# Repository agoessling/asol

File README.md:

# A Street Of Light (ASOL)
## Solar-powered LED streetlamp for A Liter Of Light (ALOL)
This design attempts to be a low-cost solar battery charger combined with a LED
driver that can be assembled and built by individuals with a large range of
experience.  The design was made using [EagleCad](http://www.cadsoftusa.com/)
and resides in the "hw" directory.  Documentation resides in the "docs"
directory.  This includes a PDF print of the schematic and PCB, a Bill Of
Materials (BOM), a design document, and the manufacturing Gerber files.  This
design is open-source and is licensed under the CERN Open Hardware License
([OHL](http://www.ohwr.org/projects/cernohl/wiki)).  It can be found in the
"license" directory.

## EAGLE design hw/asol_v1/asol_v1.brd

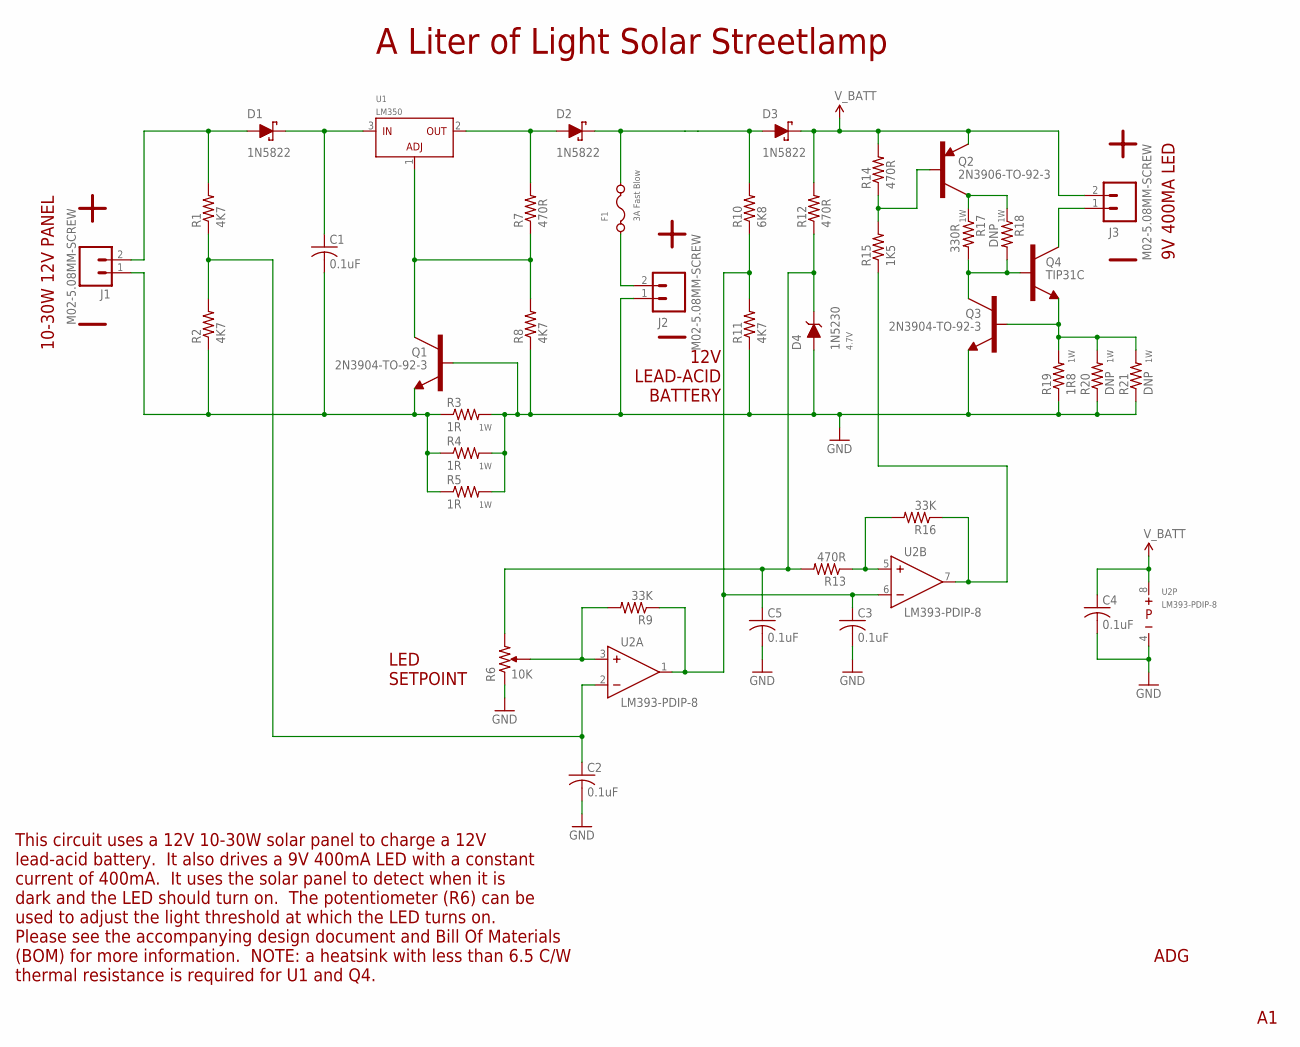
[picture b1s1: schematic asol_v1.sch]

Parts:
C1, C2, C3, C4, C5: 0.1uF; C025-025X050
D1, D2, D3: 1N5822; DO-201AD
D4: 1N5230; DO-35; VOLTAGE 4.7V
F1: 3A Fast Blow; FUSE-5X20MM
J1, J2, J3: M02-5.08MM-SCREW; SCREW-TERMINAL-5.08MM-1X2
Q1, Q3: 2N3904-TO-92-3; TO-92-3
Q2: 2N3906-TO-92-3; TO-92-3
Q4: TIP31C; TO-220-3
R1, R2, R8, R11: 4K7; 0207/12
R3, R4, R5: 1R; 0309/12
R6: 10K; POT-PTH-5X10MM
R7, R12, R13, R14: 470R; 0207/12
R9, R16: 33K; 0207/12
R10: 6K8; 0207/12
R15: 1K5; 0207/12
R17: 330R; 0309/12
R18, R20, R21: DNP; 0309/12
R19: 1R8; 0309/12
U1: LM350; TO-220-3
U2: LM393-PDIP-8; PDIP-8

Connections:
GND: C2.2, C3.2, C4.2, C5.2, D4.P$2 (A), J2.1, Q1.2 (B), Q3.1 (E), R3.2, R4.2, R5.2, R6.1, R8.1, R11.1, R19.1, R20.1, R21.1, U2.4 (NEG)
unnamed: R6.2, R9.2, U2.3 (IN+)
unnamed: J3.1, Q4.2 (C)
unnamed: Q3.2 (B), Q4.3 (E), R19.2, R20.2, R21.2
unnamed: D2.P$1 (C), D3.P$2 (A), F1.3 (2), F1.4 (2), R10.2
unnamed: Q3.3 (C), Q4.1 (B), R17.2, R18.2
unnamed: Q2.3 (C), R17.1, R18.1
unnamed: Q2.2 (B), R14.1, R15.2
unnamed: R15.1, R16.1, U2.7 (OUT)
unnamed: F1.1, F1.2 (1), J2.2
unnamed: D2.P$2 (A), R7.2, U1.2 (OUT)
unnamed: Q1.3 (C), R7.1, R8.2, U1.1 (ADJ)
unnamed: C1.2, J1.1, Q1.1 (E), R2.1, R3.1, R4.1, R5.1
unnamed: D1.P$2 (A), J1.2, R1.2
unnamed: C1.1, D1.P$1 (C), U1.3 (IN)
unnamed: R13.1, R16.2, U2.5 (IN+)
REF: C5.1, D4.P$1 (C), R6.3, R12.1, R13.2
VMEAS: C3.1, R9.1, R10.1, R11.2, U2.1 (OUT), U2.6 (IN-)
VPANEL: C2.1, R1.1, R2.2, U2.2 (IN-)
V_BATT: C4.1, D3.P$1 (C), J3.2, Q2.1 (E), R12.2, R14.2, U2.8 (POS)

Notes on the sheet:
10-30W 12V PANEL
12V LEAD-ACID BATTERY
9V 400MA LED
LED SETPOINT
ADG
This circuit uses a 12V 10-30W solar panel to charge a 12V lead-acid battery. It also drives a 9V 400mA LED with a constant current of 400mA. It uses the solar panel to detect when it is dark and the LED should turn on. The potentiometer (R6) can be used to adjust the light threshold at which the L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
A Liter of Light Solar Streetlamp

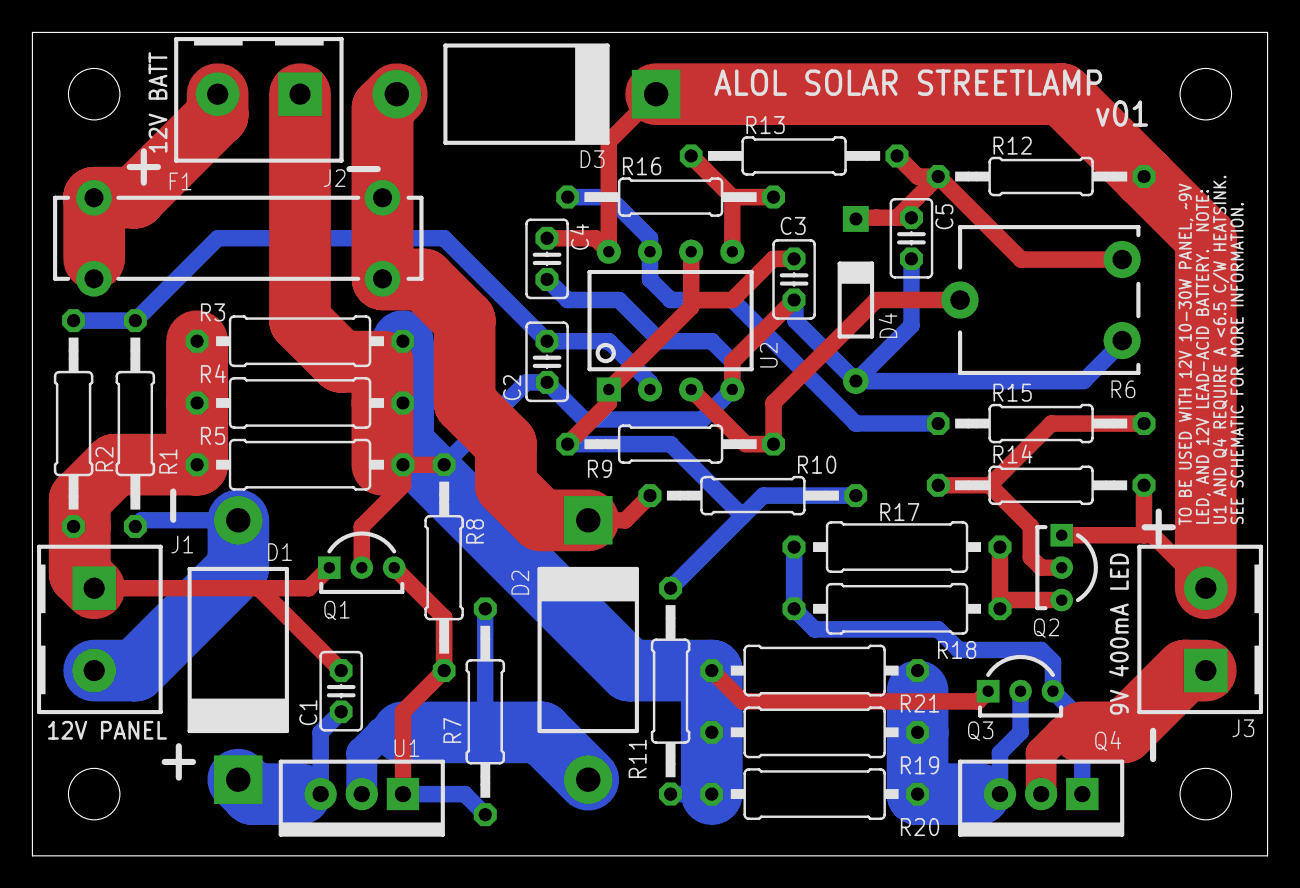
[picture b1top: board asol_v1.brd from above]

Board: 2 copper layers, 76.2 x 50.8 mm, 40 parts (0 on the bottom side), 20 nets.

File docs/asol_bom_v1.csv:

"Qty","Parts","Value","Description","VENDOR","VENDOR_PN"
,"PCB Components",,,,
5,"C1, C2, C3, C4, C5","0.1uF","CAPACITOR, American symbol","DIGIKEY","478-5741-ND"
1,"R6","10K","RESISTOR, American symbol","DIGIKEY","3319P-103-ND"
1,"R15","1K5","RESISTOR, American symbol","DIGIKEY","CF14JT1K50CT-ND"
1,"D4","1N5230","Zener Diodes","DIGIKEY","1N5230BFSCT-ND"
3,"D1, D2, D3","1N5822","Schottky Diode","DIGIKEY","497-11370-1-ND"
3,"R3, R4, R5","1R","RESISTOR, American symbol","DIGIKEY","1.0WCT-ND"
1,"R19","1R8","RESISTOR, American symbol","DIGIKEY","1.8W-1-ND"
2,"Q1, Q3","2N3904-TO-92-3","40V 200mA NPN Transistor","DIGIKEY","2N3904FS-ND"
1,"Q2","2N3906-TO-92-3","40V 200mA PNP Transistor","DIGIKEY","2N3906TFCT-ND"
1,"R17","330R","RESISTOR, American symbol","DIGIKEY","330ZCT-ND"
2,"R9, R16","33K","RESISTOR, American symbol","DIGIKEY","CF14JT33K0CT-ND"
2,"F1","3A Fast Blow","5x20mm Cartridge Fuse","DIGIKEY","507-1703-ND"
4,"R7, R12, R13, R14","470R","RESISTOR, American symbol","DIGIKEY","CF14JT470RCT-ND"
4,"R1, R2, R8, R11","4K7","RESISTOR, American symbol","DIGIKEY","CF14JT4K70CT-ND"
1,"R10","6K8","RESISTOR, American symbol","DIGIKEY","CF14JT6K80CT-ND"
2,"R20, R21","DNP","RESISTOR, American symbol","DIGIKEY","1.8W-1-ND"
1,"R18","DNP","RESISTOR, American symbol","DIGIKEY","330ZCT-ND"
1,"U1","LM350","35V 3A Linear Regulator","DIGIKEY","LM350TFS-ND"
1,"U2","LM393-PDIP-8","Dual 36V Comparator - Open Drain","DIGIKEY","296-1398-5-ND"
3,"J1, J2, J3","M02-5.08MM-SCREW","Standard 2-pin header.","DIGIKEY","ED2609-ND"
1,"Q4","TIP31C","3A 100V NPN Transistor","DIGIKEY","497-2602-5-ND"
,"Assembly Components",,,,
1,"LED COB",,"XLAMP CXA1304 LED","DIGIKEY","CXA1304-0000-000C00C20E3-ND"
1,"LED Heatsink",,"HEATSINK BLACK ANODIZED 12.7MM","DIGIKEY","SA-LED-113E-ND"
1,"Battery Fuse",,"FUSE GLASS 4A 125VAC 5X20MM","DIGIKEY","507-1268-ND"
1,"U1 and Q4 Heatsink",,"HEATSINK TO-220 FOLD 42.16MM","DIGIKEY","7020BG-ND"
4,"PCB Standoffs",,"HEX STANDOFF M3 NYLON 11MM","DIGIKEY","952-2185-ND"
4,"Standoff Screw",,"MACHINE SCREW PAN SLOTTED M3","DIGIKEY","29341K-ND"
2,"Heatsink Screw",,"MACHINE SCREW PAN PHILLIPS M3","DIGIKEY","335-1156-ND"
2,"Heatsink Nut",,"HEX NUT 0.217"" STEEL M3","DIGIKEY","KEY1149-ND"
1,"LED Heatsink Thermal Adhesive",,"Arctic Silver Arctic Alumina 5g ","AMAZON","B0087X725S"
1,"Solar Panel, Battery, and LED Wire",,"Primary Wire, 16-Gauge","AMAZON","B000PANG74"
1,"U1 and Q4 Heatsink Thermal Grease",,"Arctic Silver Arctic Alumina 14g ","AMAZON","B004Z9XG0I"
1,"Solar Panel",,"25-Watt Polycrystalline Solar Panel 12 Volt","AMAZON","B00V52ZGLU"
1,"Battery",,"12V / 18Ah Sealed Lead Acid ","AMAZON","B001C20T9C"

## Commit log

2015-07-22 Initial design commit.
    This adds the bulk of the v1 ASOL solar streetlamp.
